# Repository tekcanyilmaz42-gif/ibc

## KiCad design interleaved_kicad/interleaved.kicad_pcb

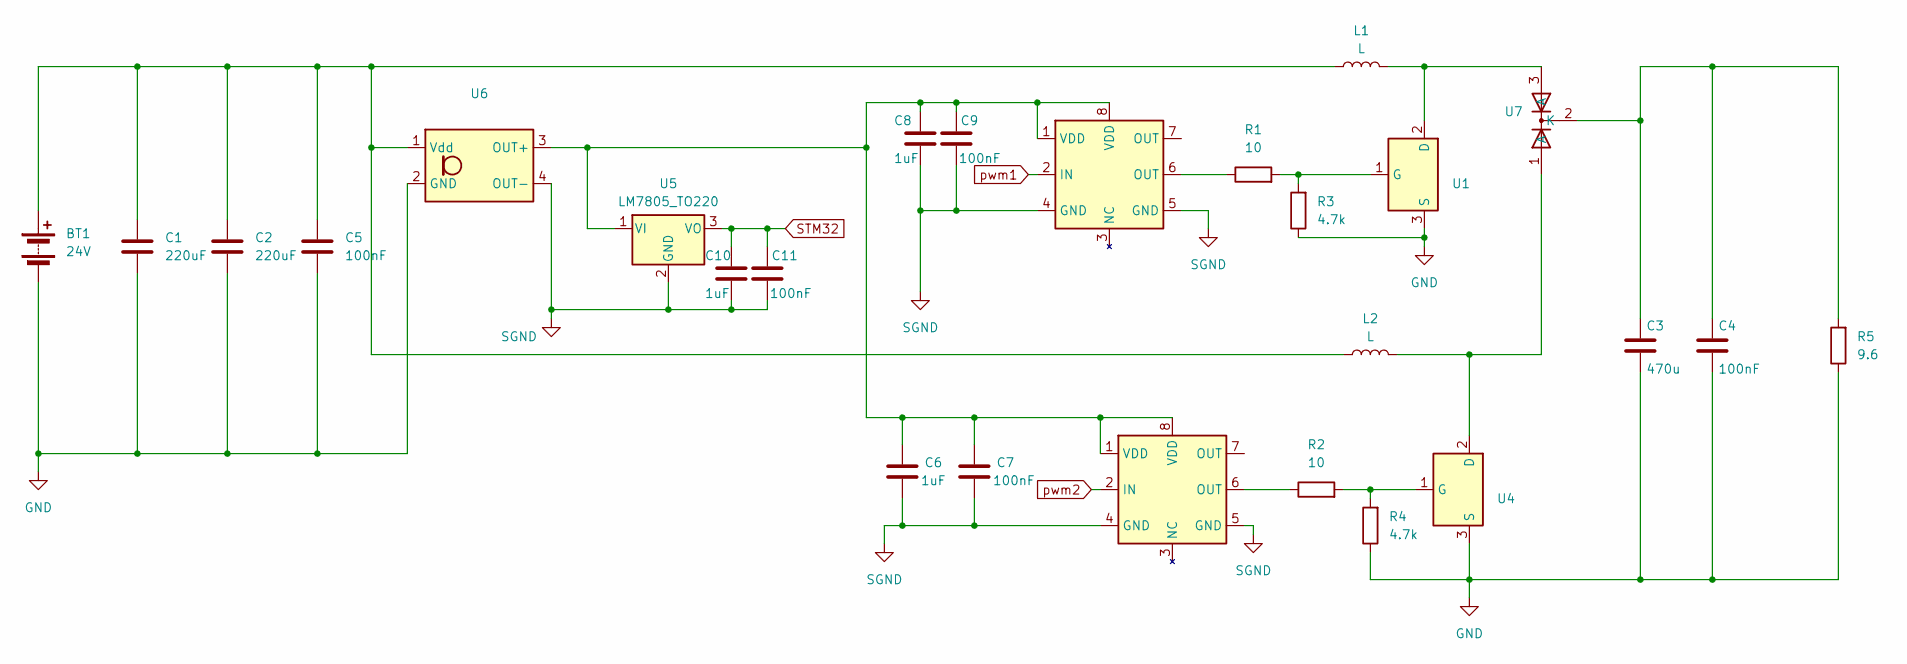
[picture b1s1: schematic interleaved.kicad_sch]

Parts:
BT1: 24V
C1, C2: 220uF; CP_Axial_L10.0mm_D4.5mm_P15.00mm_Horizontal
C3: 470u; CP_Axial_L10.0mm_D4.5mm_P15.00mm_Horizontal
C4, C5, C7, C9, C11: 100nF; CP_Axial_L10.0mm_D4.5mm_P15.00mm_Horizontal
C6, C8, C10: 1uF; CP_Axial_L10.0mm_D4.5mm_P15.00mm_Horizontal
L1, L2: L; L_Axial_L30.0mm_D8.0mm_P35.56mm_Horizontal_Fastron_77A
R1, R2: 10; R_Axial_DIN0414_L11.9mm_D4.5mm_P15.24mm_Horizontal
R3, R4: 4.7k; R_Axial_DIN0414_L11.9mm_D4.5mm_P15.24mm_Horizontal
R5: 9.6; R_Axial_Power_L48.0mm_W12.5mm_P55.88mm
U1, U4: irf640npfb
U2, U3: SOIC-8_3.9x4.9mm_P1.27mm
U5: LM7805_TO220; TO-220-3_Vertical
U6: 2596_module
U7: TO-220-3_Vertical

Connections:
GND: BT1.2 (-), C1.2, C2.2, C3.2, C4.2, C5.2, R3.1, R4.1, R5.1, U1.3 (S), U4.3 (S), U6.2 (GND)
unnamed: BT1.1 (+), C1.1, C2.1, C5.1, L1.1, L2.1, U6.1 (Vdd)
unnamed: R1.1, U2.6 (OUT)
unnamed: R2.1, U3.6 (OUT)
unnamed: L1.2, U1.2 (D), U7.3 (A)
unnamed: R1.2, R3.2, U1.1 (G)
unnamed: L2.2, U4.2 (D), U7.1 (A)
unnamed: R2.2, R4.2, U4.1 (G)
unnamed: C6.1, C7.1, C8.1, C9.1, U2.1 (VDD), U2.8 (VDD), U3.1 (VDD), U3.8 (VDD), U5.1 (VI), U6.3 (OUT+)
unnamed: C3.1, C4.1, R5.2, U7.2 (K)
SGND: C6.2, C7.2, C8.2, C9.2, C10.2, C11.2, U2.4 (GND), U2.5 (GND), U3.4 (GND), U3.5 (GND), U5.2 (GND), U6.4 (OUT-)
STM32: C10.1, C11.1, U5.3 (VO)
pwm1: U2.2 (IN)
pwm2: U3.2 (IN)

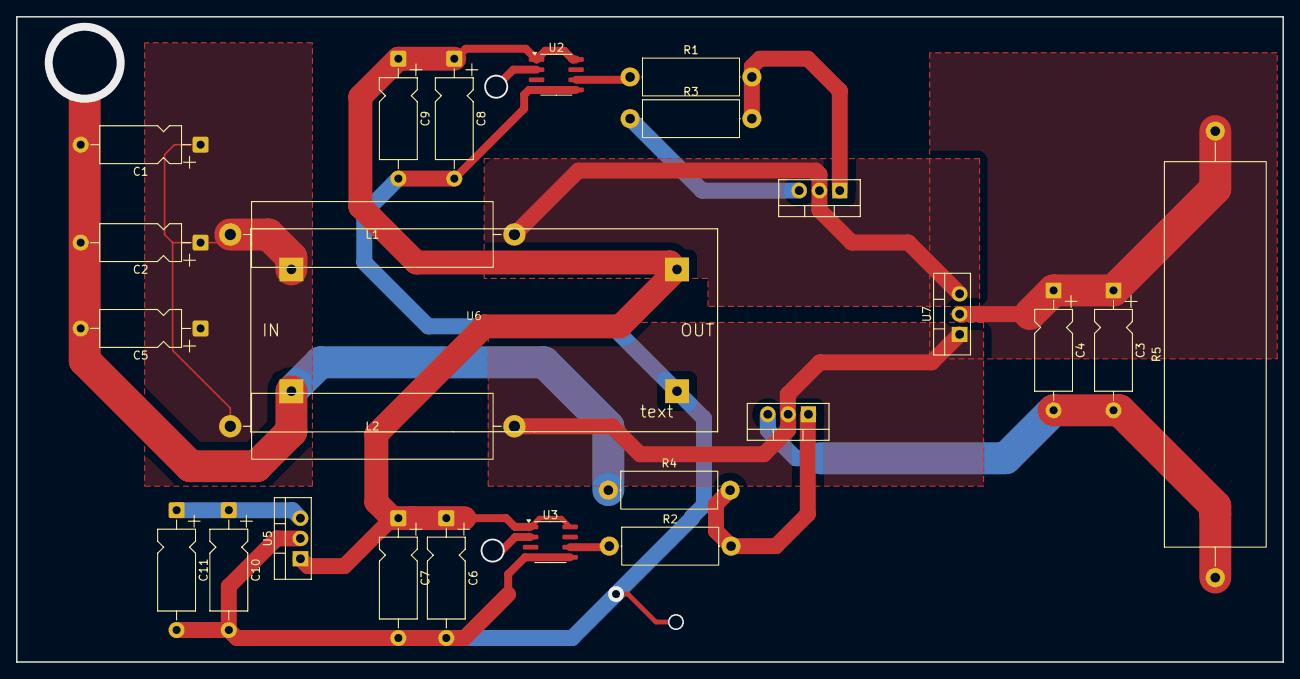
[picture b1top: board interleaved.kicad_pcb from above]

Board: 2 copper layers, 158.5 x 80.8 mm, 25 parts (0 on the bottom side), 12 nets.

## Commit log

2026-03-11 kicad
